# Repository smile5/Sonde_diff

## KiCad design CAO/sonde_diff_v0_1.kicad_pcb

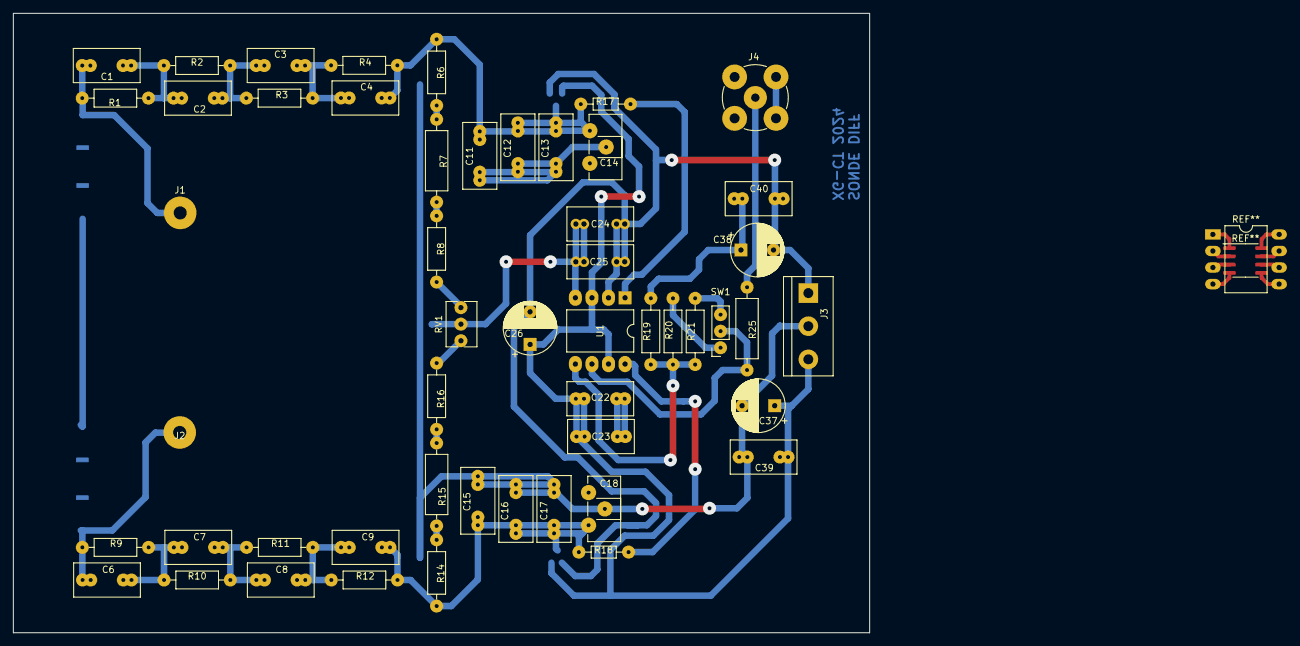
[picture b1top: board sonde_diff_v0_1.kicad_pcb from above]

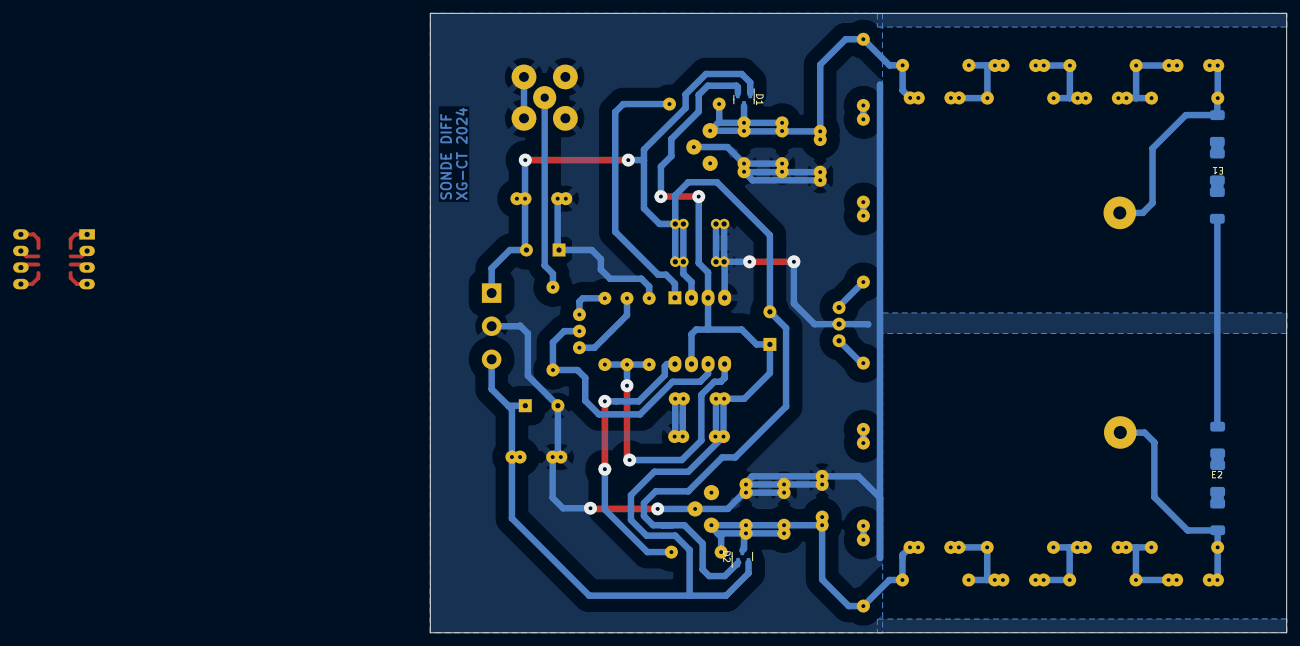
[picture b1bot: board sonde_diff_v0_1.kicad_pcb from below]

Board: 2 copper layers, 131.3 x 95.0 mm, 56 parts (4 on the bottom side), 26 nets.

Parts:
C1, C2, C3, C4, C6, C7, C8, C9: 10p; C_Rect_L10.0mm_W5.0mm_P5.00mm_P7.50mm
C11, C15: 470p; C_Rect_L10.0mm_W5.0mm_P5.00mm_P7.50mm
C12, C16: 47p; C_Rect_L10.0mm_W5.0mm_P5.00mm_P7.50mm
C13, C17: 22p; C_Rect_L10.0mm_W5.0mm_P5.00mm_P7.50mm
C14, C18: 8p; Potentiometer_ACP_CA9-H2,5_Horizontal
C22, C25, C39, C40: 100n; C_Rect_L10.0mm_W5.0mm_P5.00mm_P7.50mm
C23, C24: 100p; C_Rect_L10.0mm_W5.0mm_P5.00mm_P7.50mm
C26: 4.7u; CP_Radial_D8.0mm_P5.00mm
C37, C38: 10u; CP_Radial_D8.0mm_P5.00mm
D1, D2: BAV99; SOT-23
E1, E2: SparkGap; Spark_gap_1200
J1, J2: Conn_01x01; PIN_3mm
J3: Conn_01x03; TerminalBlock_bornier-3_P5.08mm
J4: Conn_Coaxial; BNC_TEConnectivity_1478204_Vertical
R1, R2, R3, R4, R9, R10, R11, R12: 1M; R_Axial_DIN0207_L6.3mm_D2.5mm_P10.16mm_Horizontal
R6, R14: 15k; R_Axial_DIN0207_L6.3mm_D2.5mm_P10.16mm_Horizontal
R7, R15: 2.2k; R_Axial_DIN0309_L9.0mm_D3.2mm_P12.70mm_Horizontal
R8, R16: 64; R_Axial_DIN0207_L6.3mm_D2.5mm_P10.16mm_Horizontal
R17, R18: 1500; R_Axial_DIN0204_L3.6mm_D1.6mm_P7.62mm_Horizontal
R19: 5000; R_Axial_DIN0207_L6.3mm_D2.5mm_P10.16mm_Horizontal
R20: 6000; R_Axial_DIN0207_L6.3mm_D2.5mm_P10.16mm_Horizontal
R21: 105000; R_Axial_DIN0207_L6.3mm_D2.5mm_P10.16mm_Horizontal
R25: 50; R_Axial_DIN0309_L9.0mm_D3.2mm_P12.70mm_Horizontal
RV1: 2K; Potentiometer_Bourns_3266Y_Vertical
SW1: SW_DPDT_x2; PinSocket_1x03_P2.54mm_Vertical
U1: DIP-8_W10.16mm

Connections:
GNDPWR: C11.2, C12.2, C13.2, C14.2, C15.2, C16.2, C17.2, C18.2, C22.2, C23.2, C24.2, C25.2, C37.2, C38.1, C39.2, C40.1, E1.1, E2.1, J3.2, J4.2 (Ext), R19.1, RV1.2, U1.4 (REF)
unnamed: C1.2, C2.1, R1.2, R2.1
unnamed: C2.2, C3.1, R2.2, R3.1
unnamed: C3.2, C4.1, R3.2, R4.1
unnamed: C6.2, C7.1, R9.2, R10.1
unnamed: C7.2, C8.1, R10.2, R11.1
unnamed: C8.2, C9.1, R11.2, R12.1
unnamed: C4.2, C11.1, C12.1, C13.1, C14.1, D1.3 (K), R4.2, R6.1, R17.1
unnamed: C9.2, C15.1, C16.1, C17.1, C18.1, D2.3 (K), R12.2, R14.1, R18.1
unnamed: C1.1, E1.2, J1.1, R1.1
unnamed: C6.1, E2.2, J2.1, R9.1
unnamed: J4.1 (In), R25.2
unnamed: R6.2, R7.1
unnamed: R7.2, R8.1
unnamed: R8.2, RV1.1
unnamed: R14.2, R15.1
unnamed: R15.2, R16.1
unnamed: R16.2, RV1.3
unnamed: R20.2, SW1.1 (A)
unnamed: R25.1, SW1.2 (B), U1.6
unnamed: R21.2, SW1.3 (C)
unnamed: R17.2, U1.1 (+)
unnamed: R18.2, U1.8 (-)
unnamed: R19.2, R20.1, R21.1, U1.5 (FB)
VCC: C22.1, C23.1, C26.1, C37.1, C39.1, D1.2 (A), D2.2 (A), J3.3, U1.3 (~PD), U1.7 (V+)
VEE: C24.1, C25.1, C26.2, C38.2, C40.2, D1.1 (K), D2.1 (K), J3.1, U1.2 (V-)
